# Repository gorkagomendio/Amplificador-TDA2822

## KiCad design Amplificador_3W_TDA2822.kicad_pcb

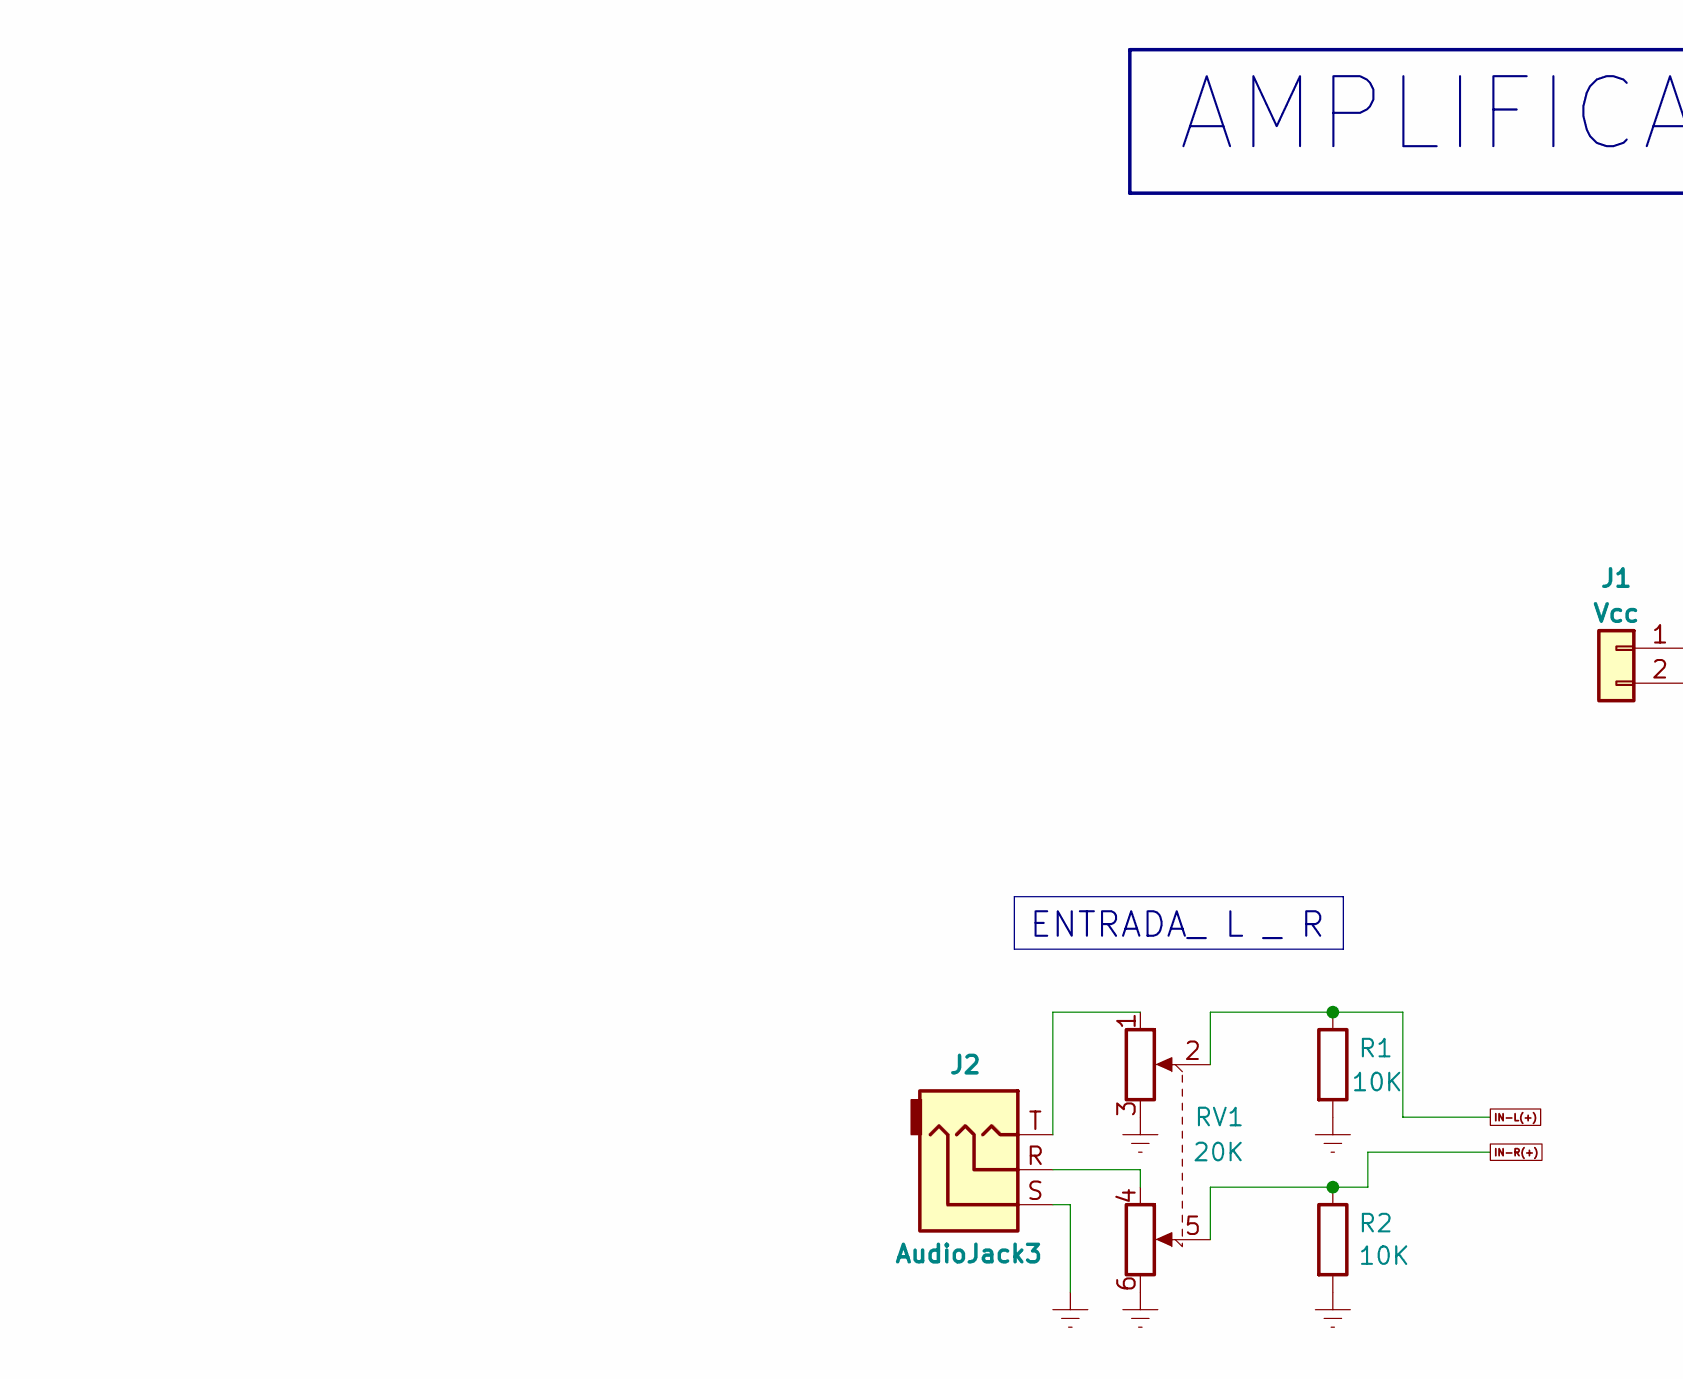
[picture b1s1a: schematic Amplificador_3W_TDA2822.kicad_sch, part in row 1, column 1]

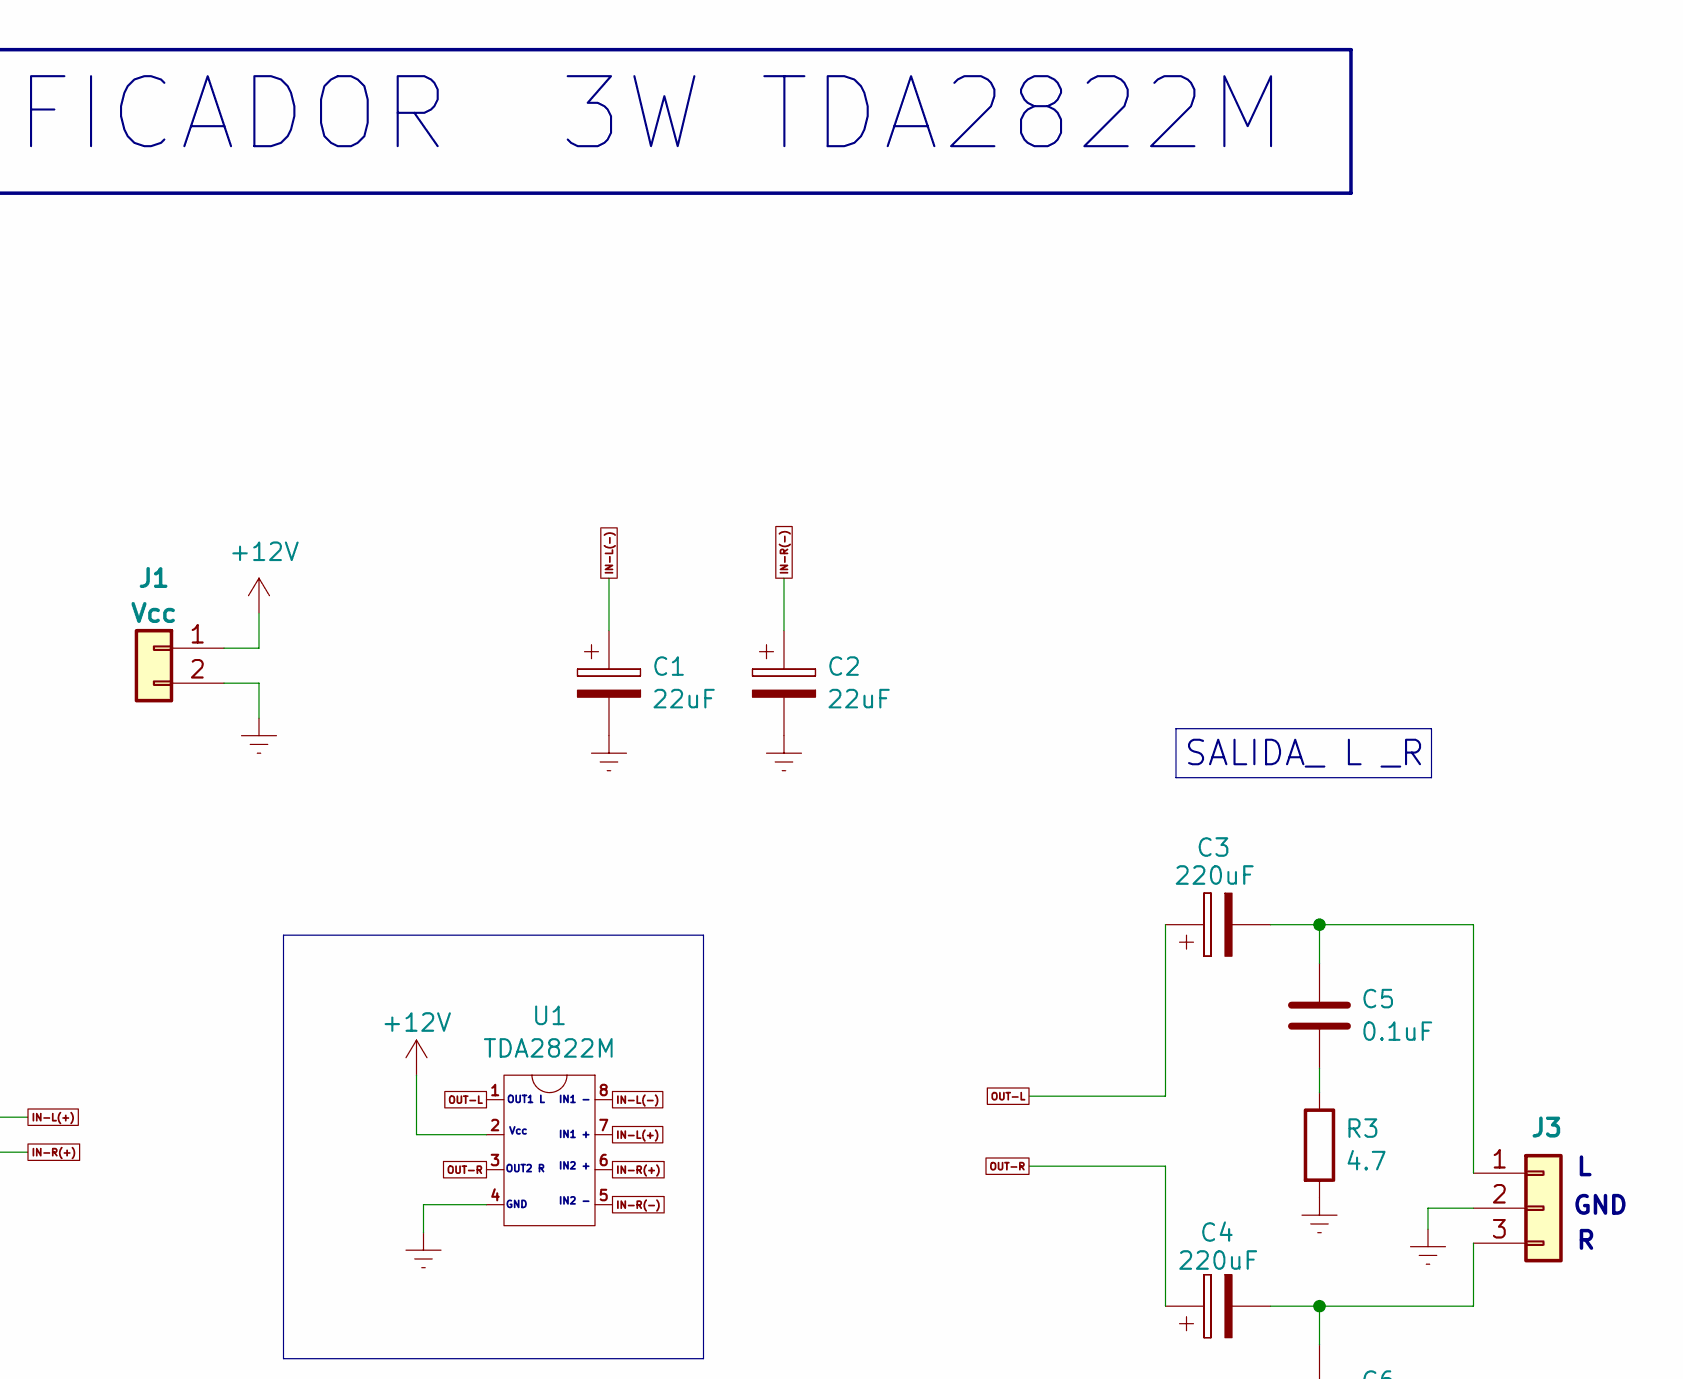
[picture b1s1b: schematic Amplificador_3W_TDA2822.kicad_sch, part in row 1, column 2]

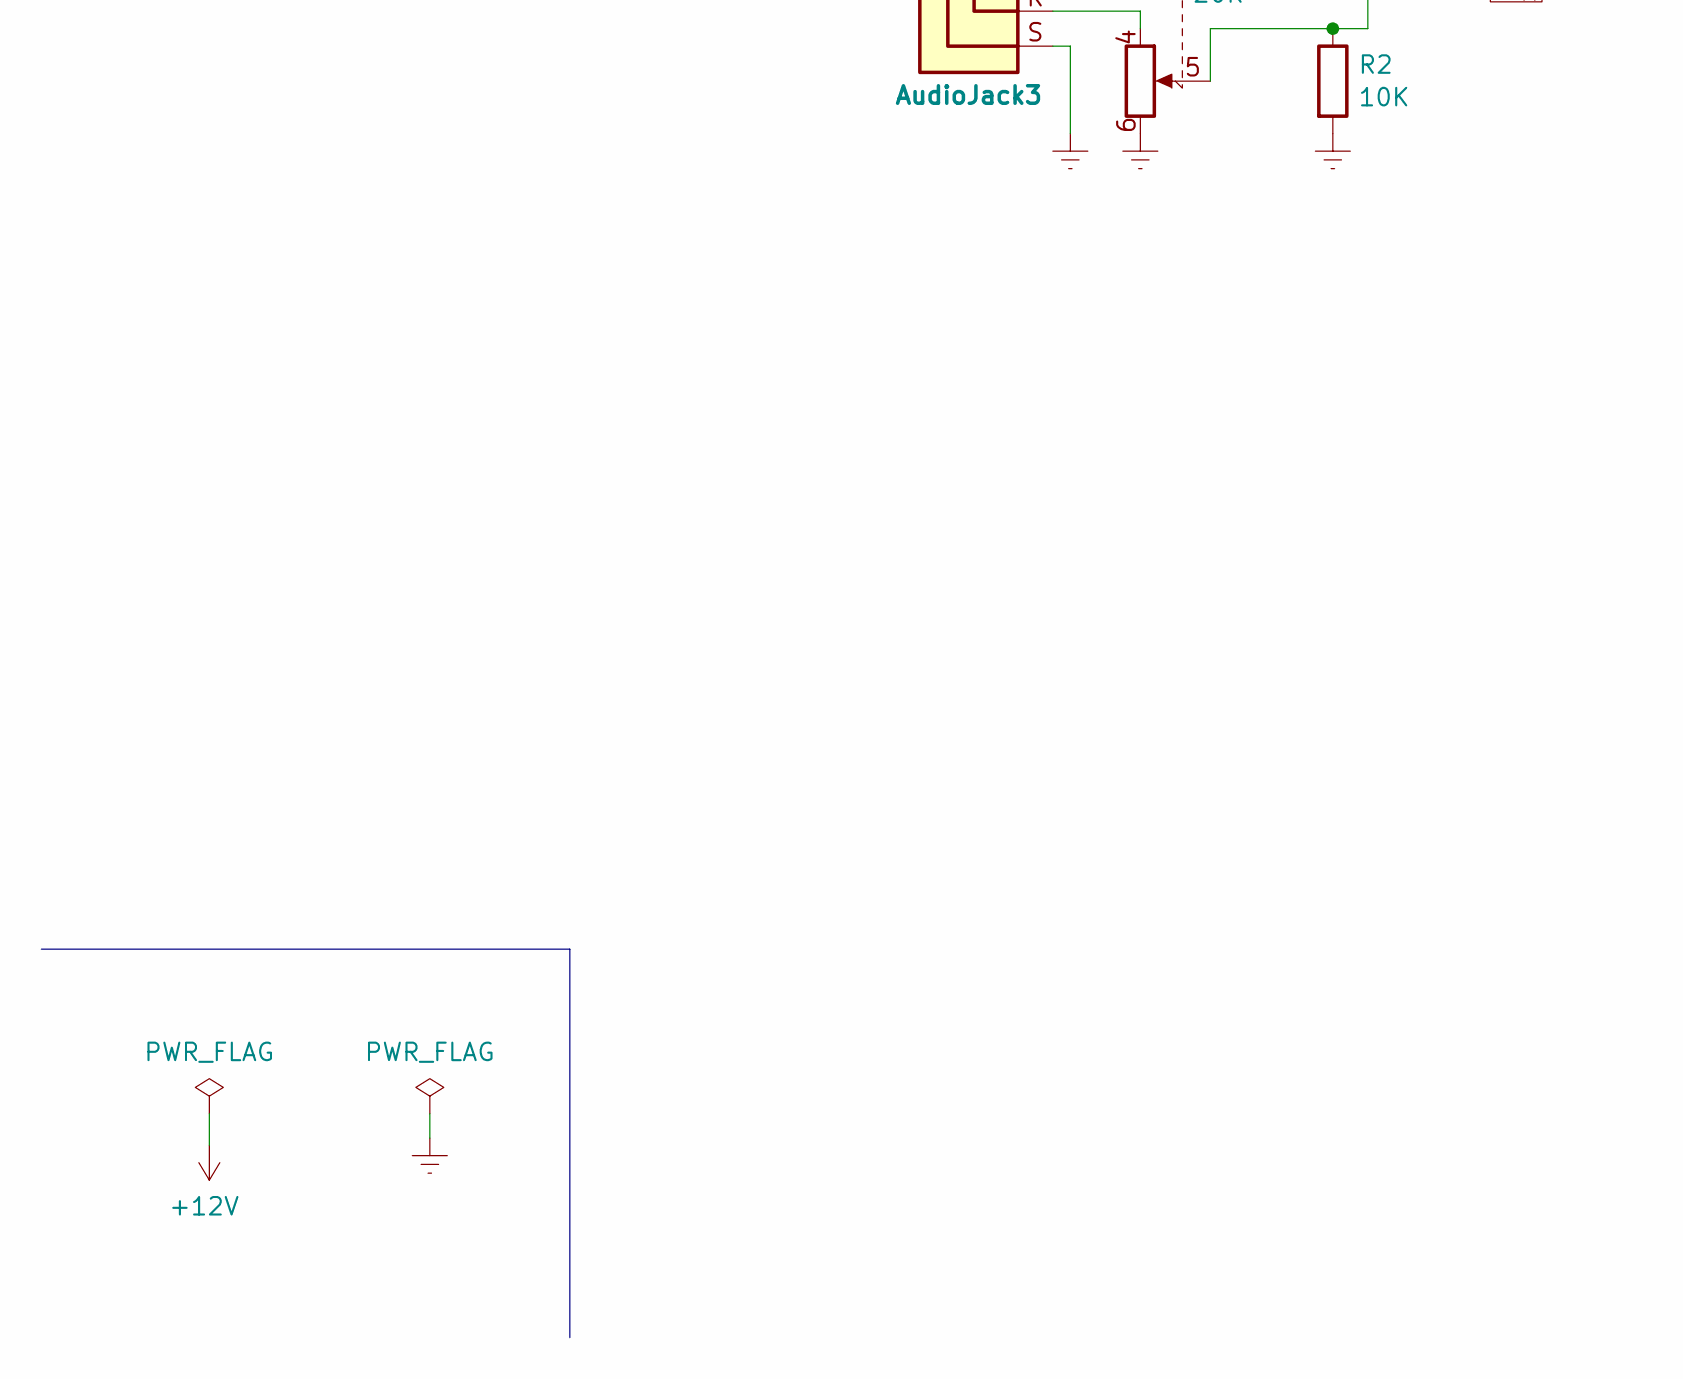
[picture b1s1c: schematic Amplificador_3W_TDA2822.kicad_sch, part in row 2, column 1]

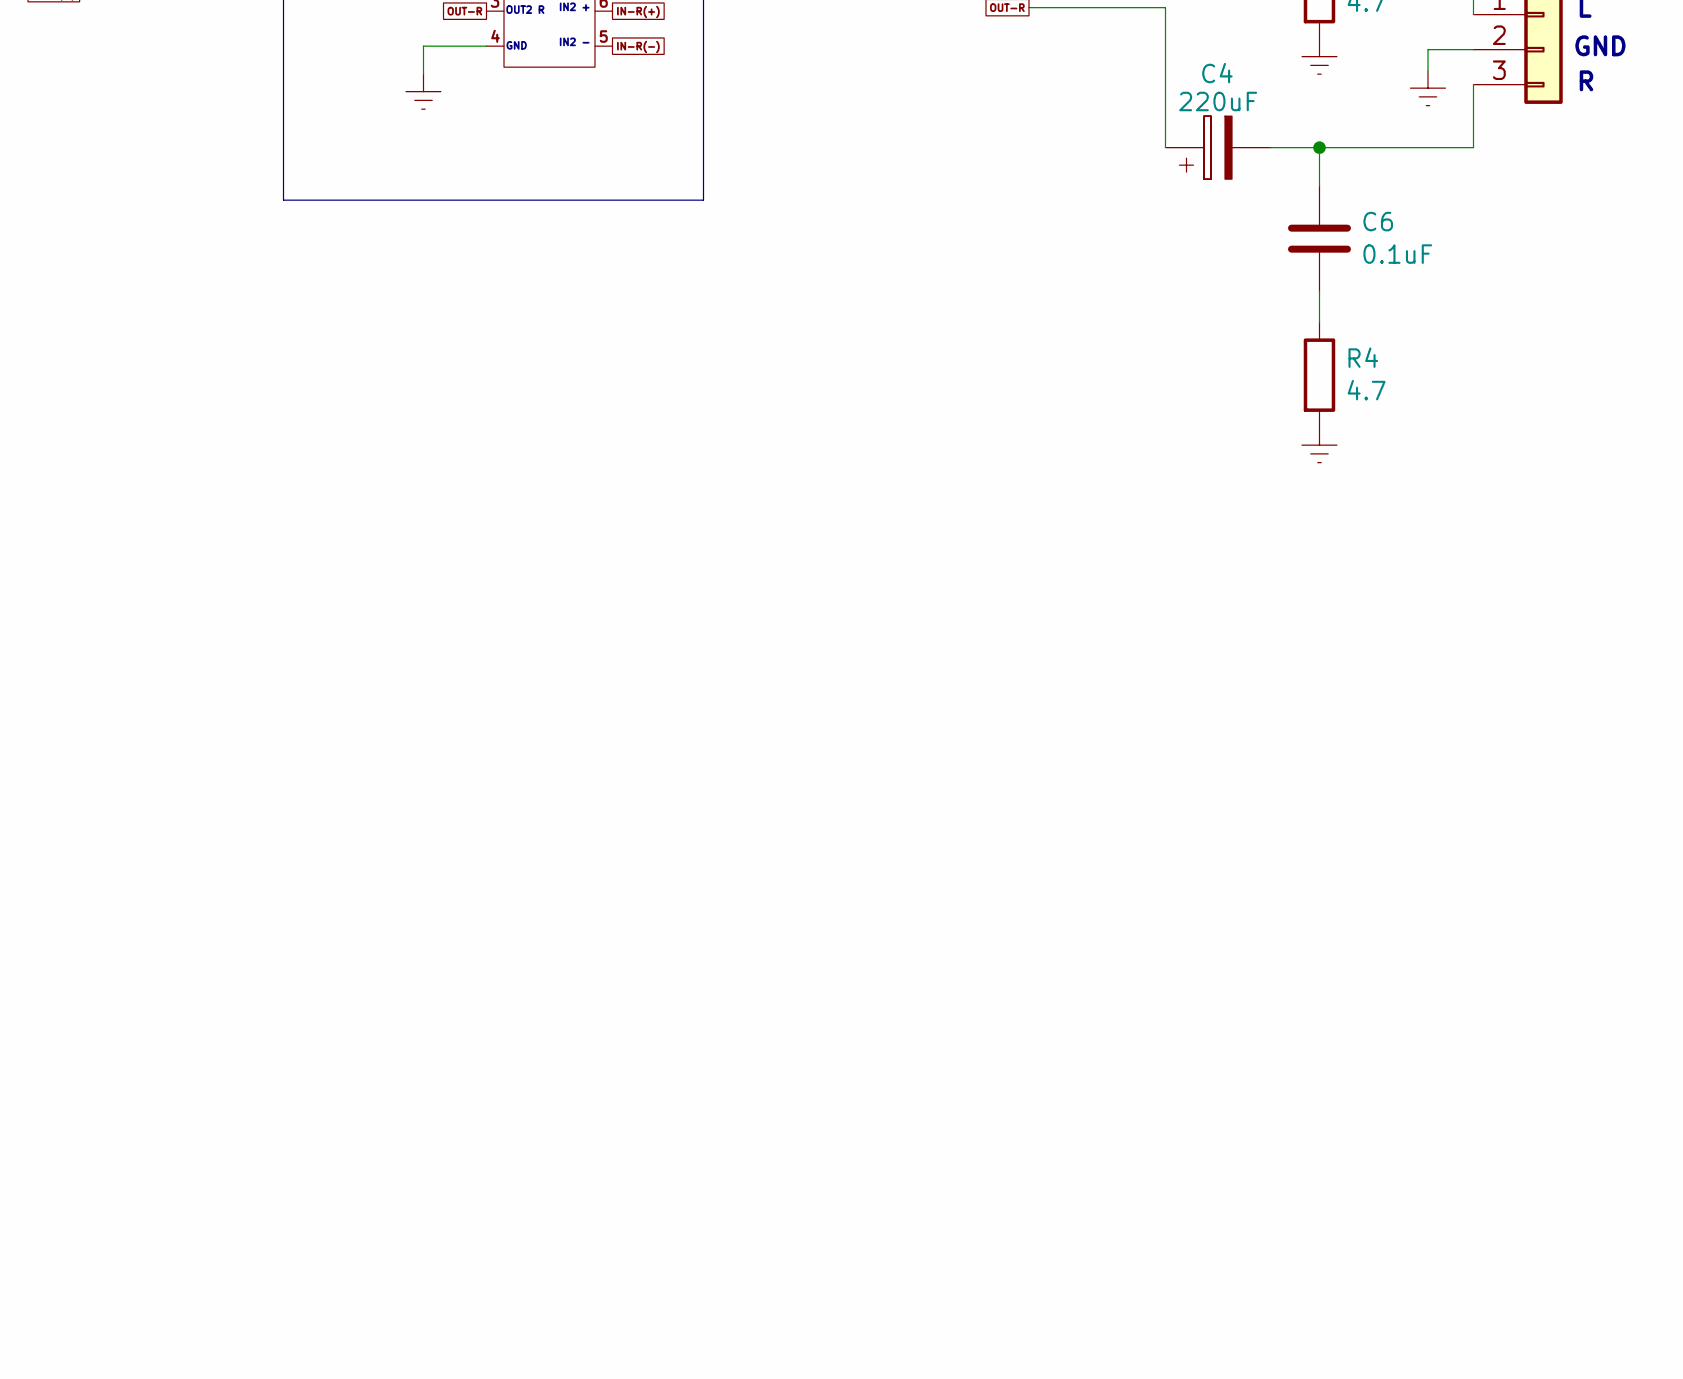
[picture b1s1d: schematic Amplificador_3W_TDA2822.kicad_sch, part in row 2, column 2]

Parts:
C1, C2: 22uF; CP_Radial_D6.3mm_P2.50mm
C3, C4: 220uF; CP_Radial_D8.0mm_P3.50mm
C5, C6: 0.1uF; C_Disc_D4.3mm_W1.9mm_P5.00mm
J1: Vcc; TerminalBlock_bornier-2_P5.08mm
J2: AudioJack3; PJ322
J3: Salida_Altavoces; TerminalBlock_bornier-3_P5.08mm
R1, R2: 10K; R_Axial_DIN0204_L3.6mm_D1.6mm_P5.08mm_Horizontal
R3, R4: 4.7; R_Axial_DIN0309_L9.0mm_D3.2mm_P12.70mm_Horizontal
RV1: 20K; Potenciometro_dual_10mm_P5mm
U1: TDA2822M; DIP-8_W7.62mm_Socket_LongPads

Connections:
+12V: J1.1, U1.2
Earth: C1.2, C2.2, J1.2, J2.S, J3.2, R1.2, R2.2, R3.2, R4.2, RV1.3, RV1.6, U1.4
IN-L(+): R1.1, RV1.2, U1.7
IN-L(-): C1.1, U1.8
IN-R(+): R2.1, RV1.5, U1.6
IN-R(-): C2.1, U1.5
unnamed: C3.2, C5.1, J3.1
unnamed: C4.2, C6.1, J3.3
unnamed: C5.2, R3.1
unnamed: C6.2, R4.1
unnamed: J2.R, RV1.4
unnamed: J2.T, RV1.1
OUT-L: C3.1, U1.1
OUT-R: C4.1, U1.3

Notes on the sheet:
OUT1 L
IN1 -
Vcc
GND
ENTRADA_ L _ R
IN2 -
AMPLIFICADOR 3W TDA2822M
SALIDA_ L _R
IN2 +
OUT2 R
IN1 +

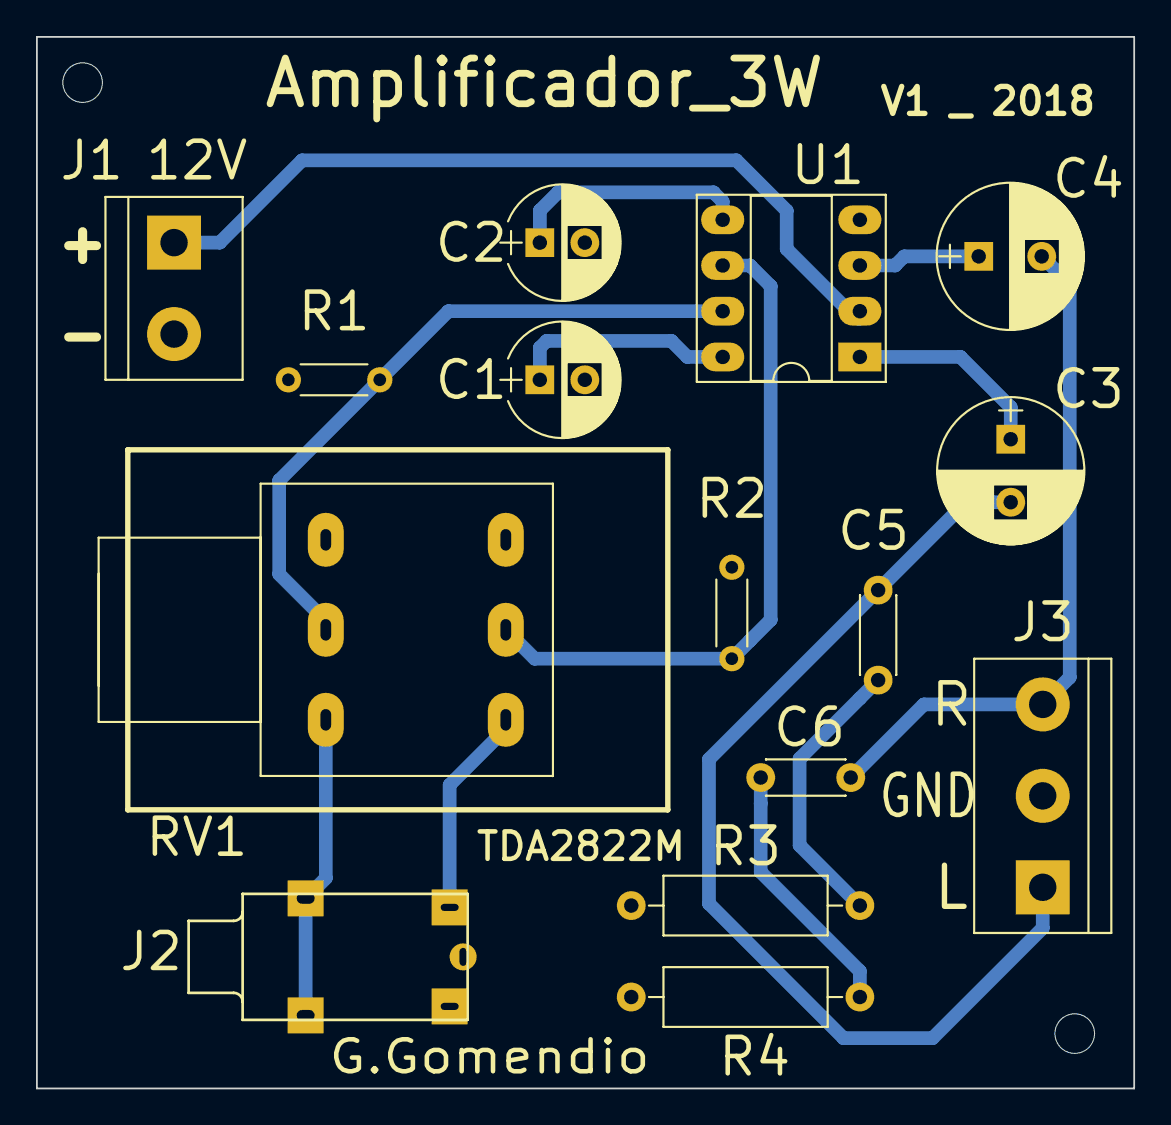
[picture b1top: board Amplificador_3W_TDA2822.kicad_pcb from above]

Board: 2 copper layers, 61.0 x 58.4 mm, 15 parts (0 on the bottom side), 14 nets.
